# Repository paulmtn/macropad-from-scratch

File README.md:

Creating a macropad from scratch starting with the PCB

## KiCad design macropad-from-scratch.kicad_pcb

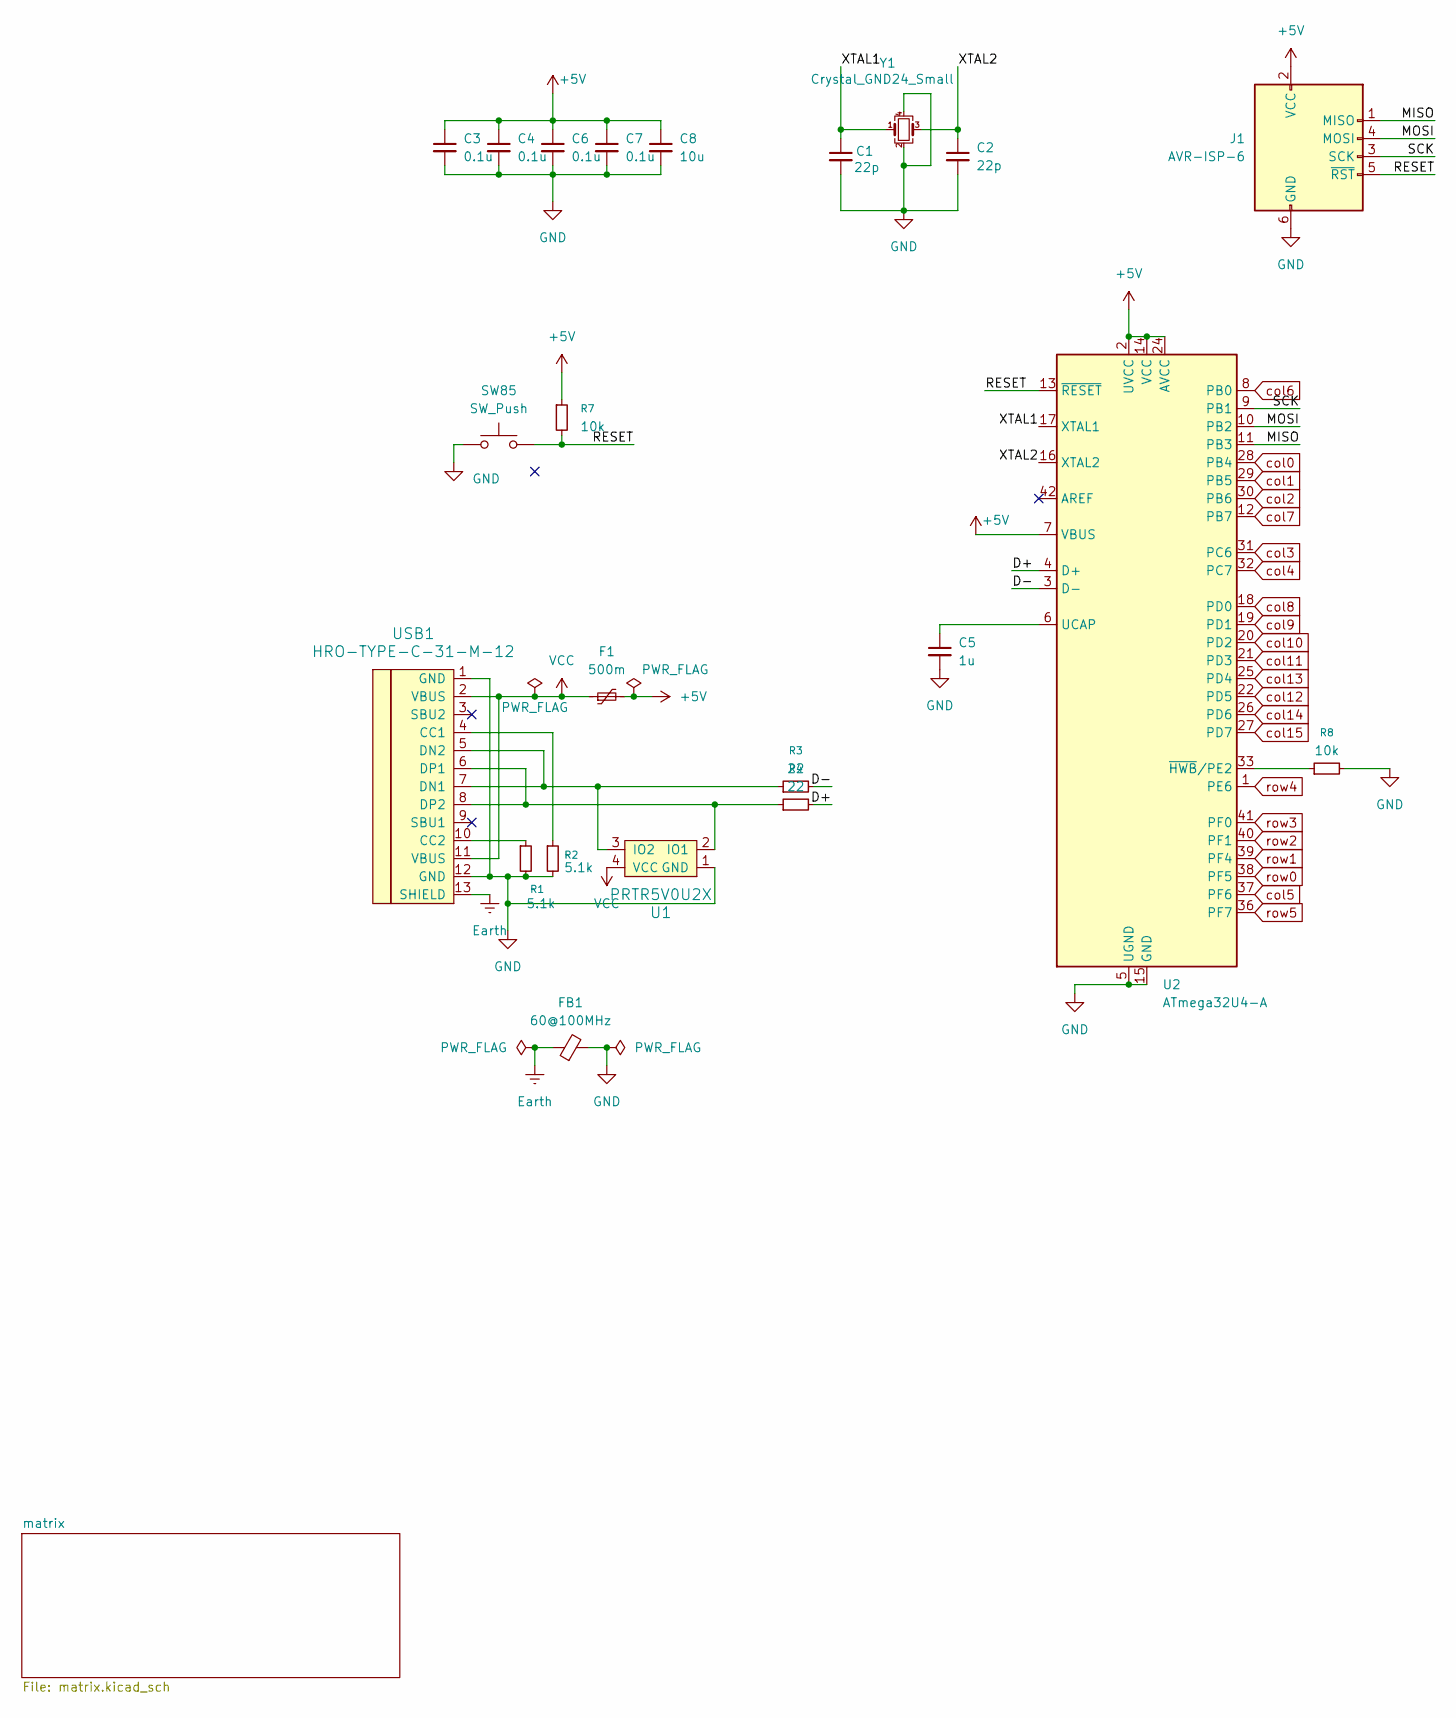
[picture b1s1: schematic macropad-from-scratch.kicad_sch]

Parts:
C1, C2: 22p; C_0805_2012Metric_Pad1.18x1.45mm_HandSolder
C3, C4, C6, C7: 0.1u; C_0805_2012Metric_Pad1.18x1.45mm_HandSolder
C5: 1u; C_0805_2012Metric_Pad1.18x1.45mm_HandSolder
C8: 10u; C_0805_2012Metric_Pad1.18x1.45mm_HandSolder
F1: 500m; Fuse_1206_3216Metric_Pad1.42x1.75mm_HandSolder
FB1: 60@100MHz; L_0805_2012Metric_Pad1.05x1.20mm_HandSolder
J1: AVR-ISP-6; Reset_Pretty-Mask
R1, R2: 5.1k; R_0805_2012Metric_Pad1.20x1.40mm_HandSolder
R3, R4: 22; R_0805_2012Metric_Pad1.20x1.40mm_HandSolder
R7, R8: 10k; R_0805_2012Metric_Pad1.20x1.40mm_HandSolder
SW85: SW_Push; SW_SPST_SKQG_WithStem
U1: PRTR5V0U2X; SOT143B
U2: ATmega32U4-A; TQFP-44_10x10mm_P0.8mm
USB1: HRO-TYPE-C-31-M-12; HRO-TYPE-C-31-M-12-HandSoldering
Y1: Crystal_GND24_Small; Crystal_SMD_3225-4Pin_3.2x2.5mm_HandSoldering

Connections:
+5V: C3.1, C4.1, C6.1, C7.1, C8.1, F1.2, J1.2 (VCC), R7.1, U2.2 (UVCC), U2.7 (VBUS), U2.14 (VCC), U2.24 (AVCC), U2.34 (VCC), U2.44 (AVCC)
/MISO: J1.1 (MISO), U2.11 (PB3)
/MOSI: J1.4 (MOSI), U2.10 (PB2)
/RESET: J1.5 (~RST), R7.2, SW85.2, U2.13 (~RESET)
/SCK: J1.3 (SCK), U2.9 (PB1)
/XTAL1: C1.1, U2.17 (XTAL1), Y1.1
/XTAL2: C2.1, U2.16 (XTAL2), Y1.3
Earth: FB1.1, USB1.13 (SHIELD)
GND: C1.2, C2.2, C3.2, C4.2, C5.2, C6.2, C7.2, C8.2, FB1.2, J1.6 (GND), R1.2, R2.2, R8.2, SW85.1, U1.1 (GND), U2.5 (UGND), U2.15 (GND), U2.23 (GND), U2.35 (GND), U2.43 (GND), USB1.1 (GND), USB1.12 (GND), Y1.2, Y1.4
unnamed: C5.1, U2.6 (UCAP)
unnamed: R8.1, U2.33 (~HWB/PE2)
unnamed: R2.1, USB1.4 (CC1)
unnamed: R1.1, USB1.10 (CC2)
VCC: F1.1, U1.4 (VCC), USB1.2 (VBUS), USB1.11 (VBUS)
col0: U2.28 (PB4); also elsewhere on the board
col1: U2.29 (PB5); also elsewhere on the board
col2: U2.30 (PB6); also elsewhere on the board
col3: U2.31 (PC6); also elsewhere on the board
col4: U2.32 (PC7); also elsewhere on the board
col5: U2.37 (PF6); also elsewhere on the board
col6: U2.8 (PB0); also elsewhere on the board
col7: U2.12 (PB7); also elsewhere on the board
col8: U2.18 (PD0); also elsewhere on the board
col9: U2.19 (PD1); also elsewhere on the board
col10: U2.20 (PD2); also elsewhere on the board
col11: U2.21 (PD3); also elsewhere on the board
col12: U2.22 (PD5); also elsewhere on the board
col13: U2.25 (PD4); also elsewhere on the board
col14: U2.26 (PD6); also elsewhere on the board
col15: U2.27 (PD7); also elsewhere on the board
row0: U2.38 (PF5); also elsewhere on the board
row1: U2.39 (PF4); also elsewhere on the board
row2: U2.40 (PF1); also elsewhere on the board
row3: U2.41 (PF0); also elsewhere on the board
row4: U2.1 (PE6); also elsewhere on the board
row5: U2.36 (PF7); also elsewhere on the board

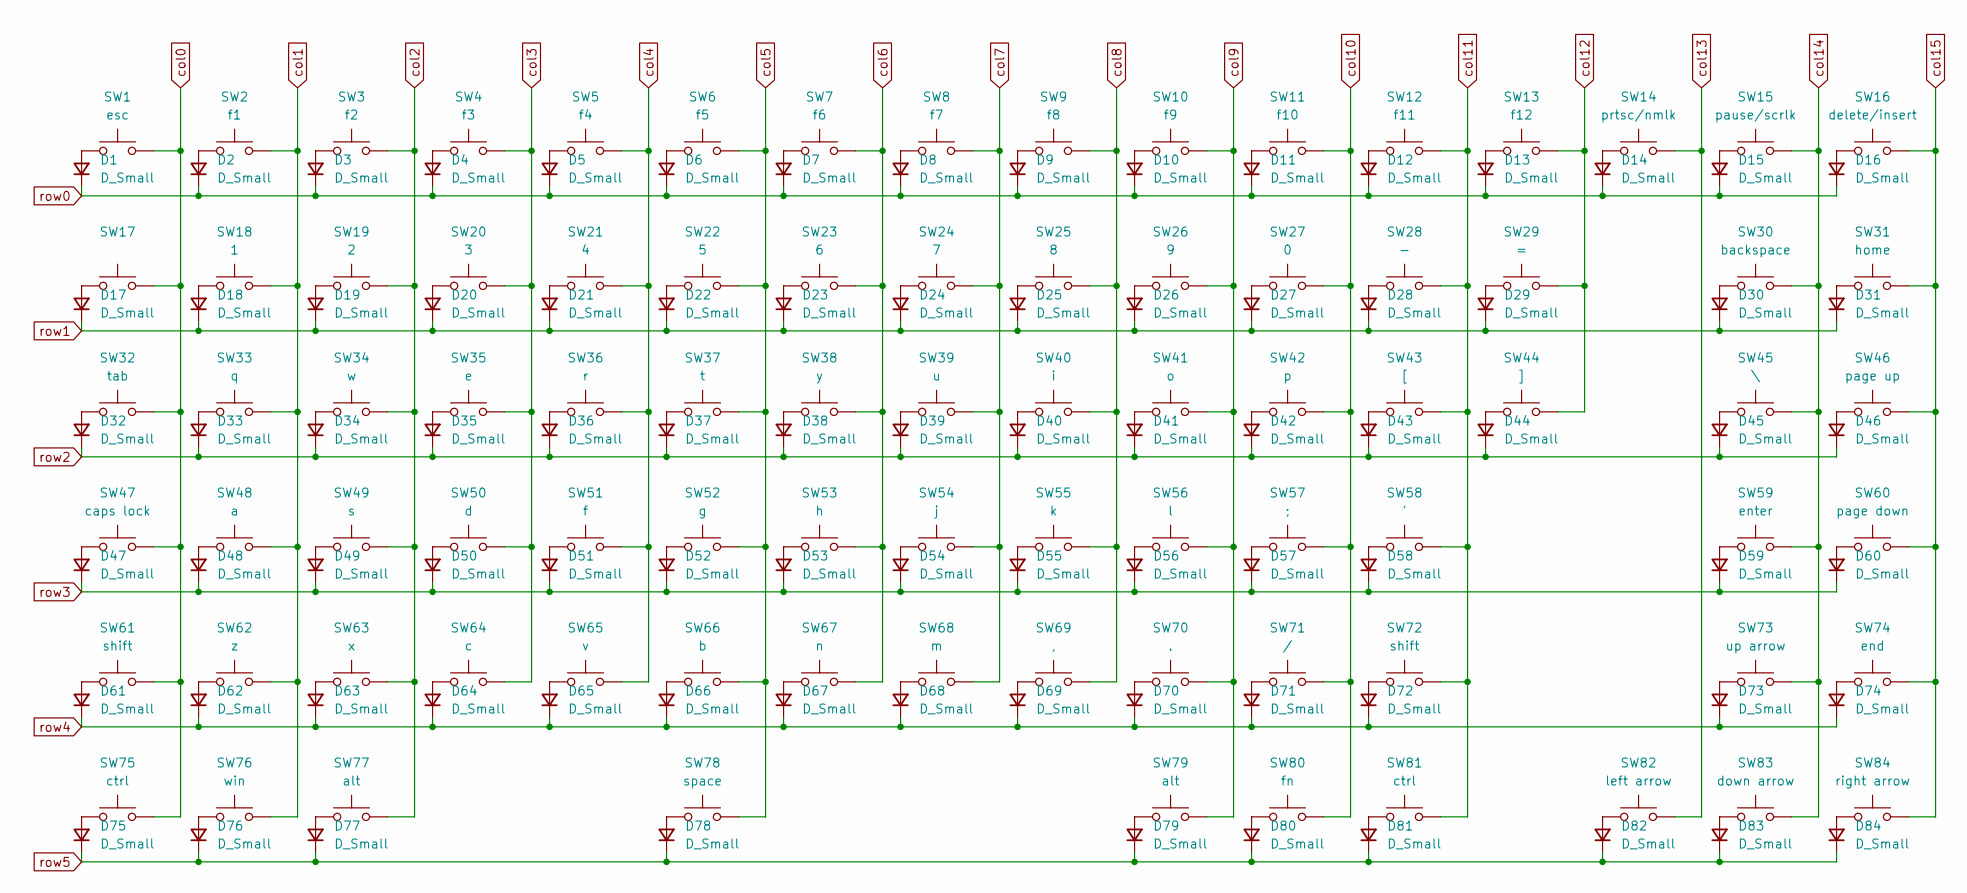
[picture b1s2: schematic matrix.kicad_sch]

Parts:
D1, D2, D3, D4, D5, D6, D7, D8, D9, D10, D11, D12, D13, D14, D15, D16, D17, D18, D19, D20, D21, D22, D23, D24, D25, D26, D27, D28, D29, D30, D31, D32, D33, D34, D35, D36, D37, D38, D39, D40, D41, D42, D43, D44, D45, D46, D47, D48, D49, D50, D51, D52, D53, D54, D55, D56, D57, D58, D59, D60, D61, D62, D63, D64, D65, D66, D67, D68, D69, D70, D71, D72, D73, D74, D75, D76, D77, D78, D79, D80, D81, D82, D83, D84: D_Small; D_SOD-123
SW1: esc; MXOnly-1U
SW2: f1; MXOnly-1U
SW3: f2; MXOnly-1U
SW4: f3; MXOnly-1U
SW5: f4; MXOnly-1U
SW6: f5; MXOnly-1U
SW7: f6; MXOnly-1U
SW8: f7; MXOnly-1U
SW9: f8; MXOnly-1U
SW10: f9; MXOnly-1U
SW11: f10; MXOnly-1U
SW12: f11; MXOnly-1U
SW13: f12; MXOnly-1U
SW14: prtsc/nmlk; MXOnly-1U
SW15: pause/scrlk; MXOnly-1U
SW16: delete/insert; MXOnly-1U
SW17: MXOnly-1U
SW18: 1; MXOnly-1U
SW19: 2; MXOnly-1U
SW20: 3; MXOnly-1U
SW21: 4; MXOnly-1U
SW22: 5; MXOnly-1U
SW23: 6; MXOnly-1U
SW24: 7; MXOnly-1U
SW25: 8; MXOnly-1U
SW26: 9; MXOnly-1U
SW27: 0; MXOnly-1U
SW28: -; MXOnly-1U
SW29: =; MXOnly-1U
SW30: backspace; MXOnly-2U
SW31: home; MXOnly-1U
SW32: tab; MXOnly-1.5U
SW33: q; MXOnly-1U
SW34: w; MXOnly-1U
SW35: e; MXOnly-1U
SW36: r; MXOnly-1U
SW37: t; MXOnly-1U
SW38: y; MXOnly-1U
SW39: u; MXOnly-1U
SW40: i; MXOnly-1U
SW41: o; MXOnly-1U
SW42: p; MXOnly-1U
SW43: [; MXOnly-1U
SW44: ]; MXOnly-1U
SW45: \; MXOnly-1.5U
SW46: page up; MXOnly-1U
SW47: caps lock; MXOnly-1.75U
SW48: a; MXOnly-1U
SW49: s; MXOnly-1U
SW50: d; MXOnly-1U
SW51: f; MXOnly-1U
SW52: g; MXOnly-1U
SW53: h; MXOnly-1U
SW54: j; MXOnly-1U
SW55: k; MXOnly-1U
SW56: l; MXOnly-1U
SW57: ;; MXOnly-1U
SW58: '; MXOnly-1U
SW59: enter; MXOnly-2.25U
SW60: page down; MXOnly-1U
SW61: shift; MXOnly-2.25U
SW62: z; MXOnly-1U
SW63: x; MXOnly-1U
SW64: c; MXOnly-1U
SW65: v; MXOnly-1U
SW66: b; MXOnly-1U
SW67: n; MXOnly-1U
SW68: m; MXOnly-1U
SW69: ,; MXOnly-1U
SW70: .; MXOnly-1U
SW71: /; MXOnly-1U
SW72: shift; MXOnly-1.75U
SW73: up arrow; MXOnly-1U
SW74: end; MXOnly-1U
SW75: ctrl; MXOnly-1.25U
SW76: win; MXOnly-1.25U
SW77: alt; MXOnly-1.25U
SW78: space; MXOnly-6.25U
SW79: alt; MXOnly-1U
SW80: fn; MXOnly-1U
SW81: ctrl; MXOnly-1U
SW82: left arrow; MXOnly-1U
SW83: down arrow; MXOnly-1U
SW84: right arrow; MXOnly-1U

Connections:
unnamed: D1.2 (A), SW1.1
unnamed: D2.2 (A), SW2.1
unnamed: D3.2 (A), SW3.1
unnamed: D4.2 (A), SW4.1
unnamed: D5.2 (A), SW5.1
unnamed: D6.2 (A), SW6.1
unnamed: D7.2 (A), SW7.1
unnamed: D8.2 (A), SW8.1
unnamed: D9.2 (A), SW9.1
unnamed: D10.2 (A), SW10.1
unnamed: D11.2 (A), SW11.1
unnamed: D12.2 (A), SW12.1
unnamed: D13.2 (A), SW13.1
unnamed: D14.2 (A), SW14.1
unnamed: D15.2 (A), SW15.1
unnamed: D16.2 (A), SW16.1
unnamed: D17.2 (A), SW17.1
unnamed: D18.2 (A), SW18.1
unnamed: D19.2 (A), SW19.1
unnamed: D20.2 (A), SW20.1
unnamed: D21.2 (A), SW21.1
unnamed: D22.2 (A), SW22.1
unnamed: D23.2 (A), SW23.1
unnamed: D24.2 (A), SW24.1
unnamed: D25.2 (A), SW25.1
unnamed: D26.2 (A), SW26.1
unnamed: D27.2 (A), SW27.1
unnamed: D28.2 (A), SW28.1
unnamed: D29.2 (A), SW29.1
unnamed: D30.2 (A), SW30.1
unnamed: D31.2 (A), SW31.1
unnamed: D32.2 (A), SW32.1
unnamed: D33.2 (A), SW33.1
unnamed: D34.2 (A), SW34.1
unnamed: D35.2 (A), SW35.1
unnamed: D36.2 (A), SW36.1
unnamed: D37.2 (A), SW37.1
unnamed: D38.2 (A), SW38.1
unnamed: D39.2 (A), SW39.1
unnamed: D40.2 (A), SW40.1
unnamed: D41.2 (A), SW41.1
unnamed: D42.2 (A), SW42.1
unnamed: D43.2 (A), SW43.1
unnamed: D44.2 (A), SW44.1
unnamed: D45.2 (A), SW45.1
unnamed: D46.2 (A), SW46.1
unnamed: D47.2 (A), SW47.1
unnamed: D48.2 (A), SW48.1
unnamed: D49.2 (A), SW49.1
unnamed: D50.2 (A), SW50.1
unnamed: D51.2 (A), SW51.1
unnamed: D52.2 (A), SW52.1
unnamed: D53.2 (A), SW53.1
unnamed: D54.2 (A), SW54.1
unnamed: D55.2 (A), SW55.1
unnamed: D56.2 (A), SW56.1
unnamed: D57.2 (A), SW57.1
unnamed: D58.2 (A), SW58.1
unnamed: D59.2 (A), SW59.1
unnamed: D60.2 (A), SW60.1
unnamed: D61.2 (A), SW61.1
unnamed: D62.2 (A), SW62.1
unnamed: D63.2 (A), SW63.1
unnamed: D64.2 (A), SW64.1
unnamed: D65.2 (A), SW65.1
unnamed: D66.2 (A), SW66.1
unnamed: D67.2 (A), SW67.1
unnamed: D68.2 (A), SW68.1
unnamed: D69.2 (A), SW69.1
unnamed: D70.2 (A), SW70.1
unnamed: D71.2 (A), SW71.1
unnamed: D72.2 (A), SW72.1
unnamed: D73.2 (A), SW73.1
unnamed: D74.2 (A), SW74.1
unnamed: D75.2 (A), SW75.1
unnamed: D76.2 (A), SW76.1
unnamed: D77.2 (A), SW77.1
unnamed: D78.2 (A), SW78.1
unnamed: D79.2 (A), SW79.1
unnamed: D80.2 (A), SW80.1
unnamed: D81.2 (A), SW81.1
unnamed: D82.2 (A), SW82.1
unnamed: D83.2 (A), SW83.1
unnamed: D84.2 (A), SW84.1
col0: SW1.2, SW17.2, SW32.2, SW47.2, SW61.2, SW75.2; also elsewhere on the board
col1: SW2.2, SW18.2, SW33.2, SW48.2, SW62.2, SW76.2; also elsewhere on the board
col2: SW3.2, SW19.2, SW34.2, SW49.2, SW63.2, SW77.2; also elsewhere on the board
col3: SW4.2, SW20.2, SW35.2, SW50.2, SW64.2; also elsewhere on the board
col4: SW5.2, SW21.2, SW36.2, SW51.2, SW65.2; also elsewhere on the board
col5: SW6.2, SW22.2, SW37.2, SW52.2, SW66.2, SW78.2; also elsewhere on the board
col6: SW7.2, SW23.2, SW38.2, SW53.2, SW67.2; also elsewhere on the board
col7: SW8.2, SW24.2, SW39.2, SW54.2, SW68.2; also elsewhere on the board
col8: SW9.2, SW25.2, SW40.2, SW55.2, SW69.2; also elsewhere on the board
col9: SW10.2, SW26.2, SW41.2, SW56.2, SW70.2, SW79.2; also elsewhere on the board
col10: SW11.2, SW27.2, SW42.2, SW57.2, SW71.2, SW80.2; also elsewhere on the board
col11: SW12.2, SW28.2, SW43.2, SW58.2, SW72.2, SW81.2; also elsewhere on the board
col12: SW13.2, SW29.2, SW44.2; also elsewhere on the board
col13: SW14.2, SW82.2; also elsewhere on the board
col14: SW15.2, SW30.2, SW45.2, SW59.2, SW73.2, SW83.2; also elsewhere on the board
col15: SW16.2, SW31.2, SW46.2, SW60.2, SW74.2, SW84.2; also elsewhere on the board
row0: D1.1 (K), D2.1 (K), D3.1 (K), D4.1 (K), D5.1 (K), D6.1 (K), D7.1 (K), D8.1 (K), D9.1 (K), D10.1 (K), D11.1 (K), D12.1 (K), D13.1 (K), D14.1 (K), D15.1 (K), D16.1 (K); also elsewhere on the board
row1: D17.1 (K), D18.1 (K), D19.1 (K), D20.1 (K), D21.1 (K), D22.1 (K), D23.1 (K), D24.1 (K), D25.1 (K), D26.1 (K), D27.1 (K), D28.1 (K), D29.1 (K), D30.1 (K), D31.1 (K); also elsewhere on the board
row2: D32.1 (K), D33.1 (K), D34.1 (K), D35.1 (K), D36.1 (K), D37.1 (K), D38.1 (K), D39.1 (K), D40.1 (K), D41.1 (K), D42.1 (K), D43.1 (K), D44.1 (K), D45.1 (K), D46.1 (K); also elsewhere on the board
row3: D47.1 (K), D48.1 (K), D49.1 (K), D50.1 (K), D51.1 (K), D52.1 (K), D53.1 (K), D54.1 (K), D55.1 (K), D56.1 (K), D57.1 (K), D58.1 (K), D59.1 (K), D60.1 (K); also elsewhere on the board
row4: D61.1 (K), D62.1 (K), D63.1 (K), D64.1 (K), D65.1 (K), D66.1 (K), D67.1 (K), D68.1 (K), D69.1 (K), D70.1 (K), D71.1 (K), D72.1 (K), D73.1 (K), D74.1 (K); also elsewhere on the board
row5: D75.1 (K), D76.1 (K), D77.1 (K), D78.1 (K), D79.1 (K), D80.1 (K), D81.1 (K), D82.1 (K), D83.1 (K), D84.1 (K); also elsewhere on the board

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
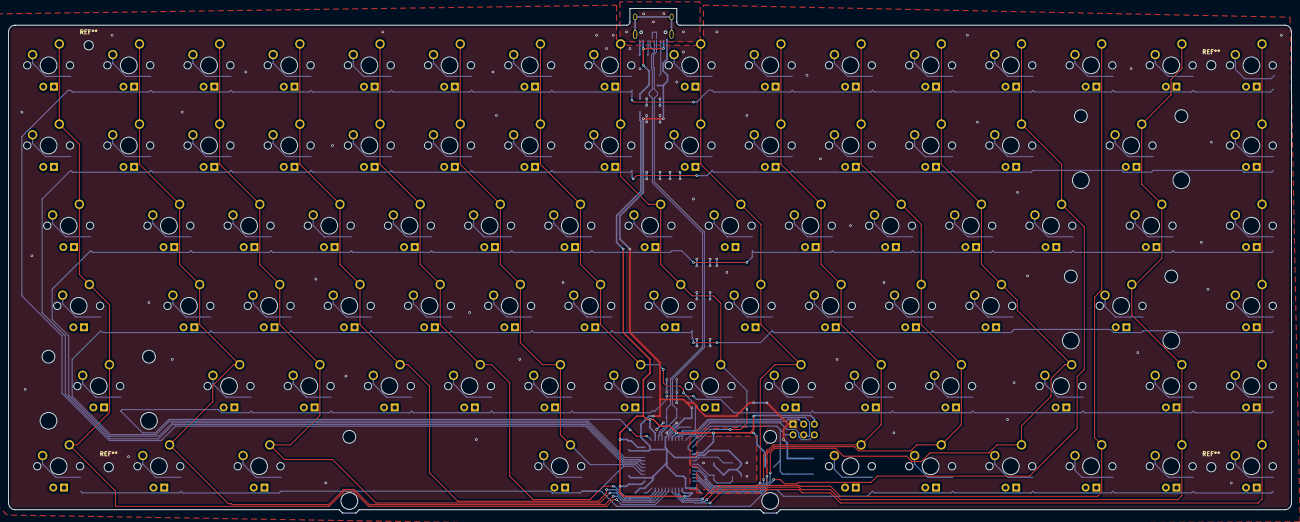
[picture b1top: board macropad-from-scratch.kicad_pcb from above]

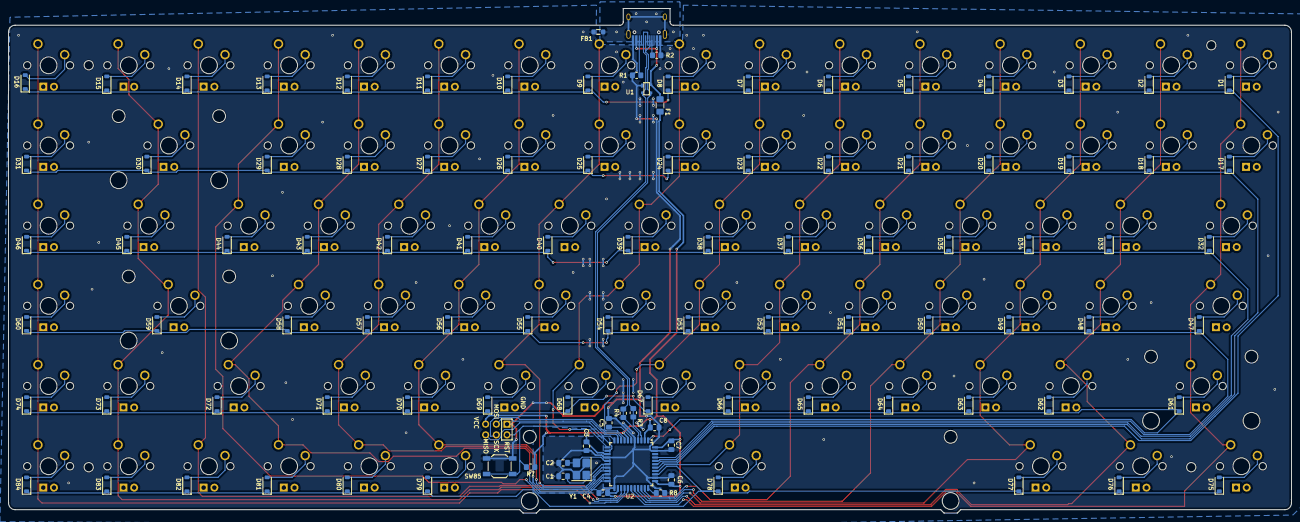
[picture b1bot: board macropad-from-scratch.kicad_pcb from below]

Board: 2 copper layers, 304.8 x 119.9 mm, 190 parts (106 on the bottom side), 122 nets.

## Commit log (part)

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2025-12-09 edit README and add the pcb files
2025-12-09 add submodules
2025-12-09 added submodules to kicad
2025-12-09 added the MCU, some resistors, and a capacitor
2025-12-21 Added keyboard matrix
2026-01-01 completed pcb
2026-01-01 routed columns
2026-01-09 routed the matrix
